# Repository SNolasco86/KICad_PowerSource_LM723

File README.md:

# Mecatronica I Fuente 18V 3A en base regulador de tensión LM723
Placa para realizar la fuente de Mecatrónica I regulable en tensión (1,2V a 18V) con limitador de corriente (0.1A a 3A).
Tambien está diseñada para poder conectarla con un voltimetro/amperimetro disponible en el mercado para ser colocada en el propio gabinete.

# Vistas

# Recursos
La placa permite generar señales eléctricas como así también recibir señales desde circuitos externos. El esqumático puede verse en este [PDF](https://github.com/SNolasco86/KICad_PowerSource_LM723/tree/main/sch/Board.pdf).

# Consideraciones de la Placa
## Gerbers
Los archivos Gerbers que están en este directorio [[link](https://github.com/SNolasco86/KICad_PowerSource_LM723/tree/main/release/)] contienen todo lo necesario para realizar la fabricación de la placa en forma industrial. Es decir, pueden ser proporcionados a cualquier fabricante de placas. En las mismas extenciones de dichos archivos se encuentran información de las capas con las que fue diseñada esta placa. Para conocer e interpretar el formato de cada extensión puede revisarse la siguiente publicación [link](https://www.proto-electronics.com/es/blog/archivos-gerber-para-qe-sirven).

## PDFs
Se exportan las diferentes capas de la placa en formato PDF de forma tal que pueda ser diseñado en forma manual. Existen diferentes métodos "caseros" con los que se puede llevar adelante la fabricación de una placa siempre y cuando el diseño lo permita. Esto quiere decir que no cualquier diseño PCB puede ser fabricado en forma manual. Esto se deben a las siguientes condiciones:
 - **Paso mínimo:** Es la mínima resolución que se considera en todo el diseño. Esto se tiene en cuenta tanto en la resolución de una pista como el margen de los pads. En el caso de intentar realizar la placa con los métodos de planchado o luz ultravioleta, aquellas placas con pasos mínimos muy pequeños son dificil de lograr.
 - **Pistas de cobre:** Los proceso de fabricación logran obtener las pistas de cobre con diferentes resoluciones según el requerimiento del cliente. En caso de querer realizar las pistas sobre una placa simple faz se debe utilizar diferentes métodos. A continuación se listan los dos métodos más comunes:
    - **Método con plancha:** Este método consiste en imprimir la capa, donde se tienen las pistas de cobre, en una hoja satinada (revistas o papel fotográfico) con una impresora laser y luego se transfiere esta impresión al pedazo de placa. En el siguiente enlace se muestra el proceso [link](https://www.neoteo.com/circuitos-impresos-el-metodo-de-la-plancha/). 
    - **Método con luz UV:** En este método se requieren más elementos complejos que el primero. Se utiliza una una hoja plástica transparente  para realizar la impresión, una pintura especial que será depositada en la placa como así también es importante tener una cámara con luz UV. Una muestra de este proceso puede verse en el siguiente enlace [link](http://uedesign.com.ar/PDFs/M%C3%A9todo_UV.pdf).

    Como se dijo anteriormente, son procesos compejos de lograr y se requiere de varios intentos. Una vez obtenida la placa con las pistas pintadas, el proceso de reacción química para remover las áreas de cobre es **peligroso** y debe tomarse todas las medidas se seguridad pertinentes. Aquí algunas referencias sobre seguridad [link](https://aulavirtual.fio.unam.edu.ar/pluginfile.php/61611/mod_resource/content/1/Seguridad%20en%20los%20laboratorios%20qu%C3%ADmicos.pdf).

 - **Máscaras anti-soldantes:** Todas las placas fabricadas industrialmente tienen, en sus capas con pistas de cobre, una máscara con una pintura anti-soldante. Esto evita que el estaño en el proceso de soldadura no se propague por todas las pistas y únicamente queden depositados en los pads. Esta casa es casi imposible de realizar en forma manual, existen técnicas pero son muy costosas y poco recomendables.
 - **Perforaciones:** Los fabricantes de placas tienen herramientas que permiten una exactitud en las perforaciones, además de complir con las secciones requeridas. En caso de realizarla manualmente este proceso podría contener errores propios de la manipulación manual y falto de precisión.

## Capas
La placa está diseñada para ser fabricada a simple faz. En los archivos [PDF](https://github.com/SNolasco86/KICad_PowerSource_LM723/tree/main/pcb/) de fabricación se pueden identificar dos capas:
 - **Capa Superior [[minilab-F.Cu.pdf](https://github.com/SNolasco86/KICad_PowerSource_LM723/blob/main/pcb/Top.pdf)]:** En esta capa se colocarán los componentes electrónicos y en caso de fabricar manualmente la placa, se deberá insertar los cables-puentes de la placa. Estos "puentes" emulan las coneciones de la capa inferior. 
 - **Capa inferior[[minilab-B.Cu.pdf](https://github.com/SNolasco86/KICad_PowerSource_LM723/blob/main/pcb/Bottom.pdf)]:** Es la capa dónde se trandrán las pistas de cobre y se realizarán las soldaduras.

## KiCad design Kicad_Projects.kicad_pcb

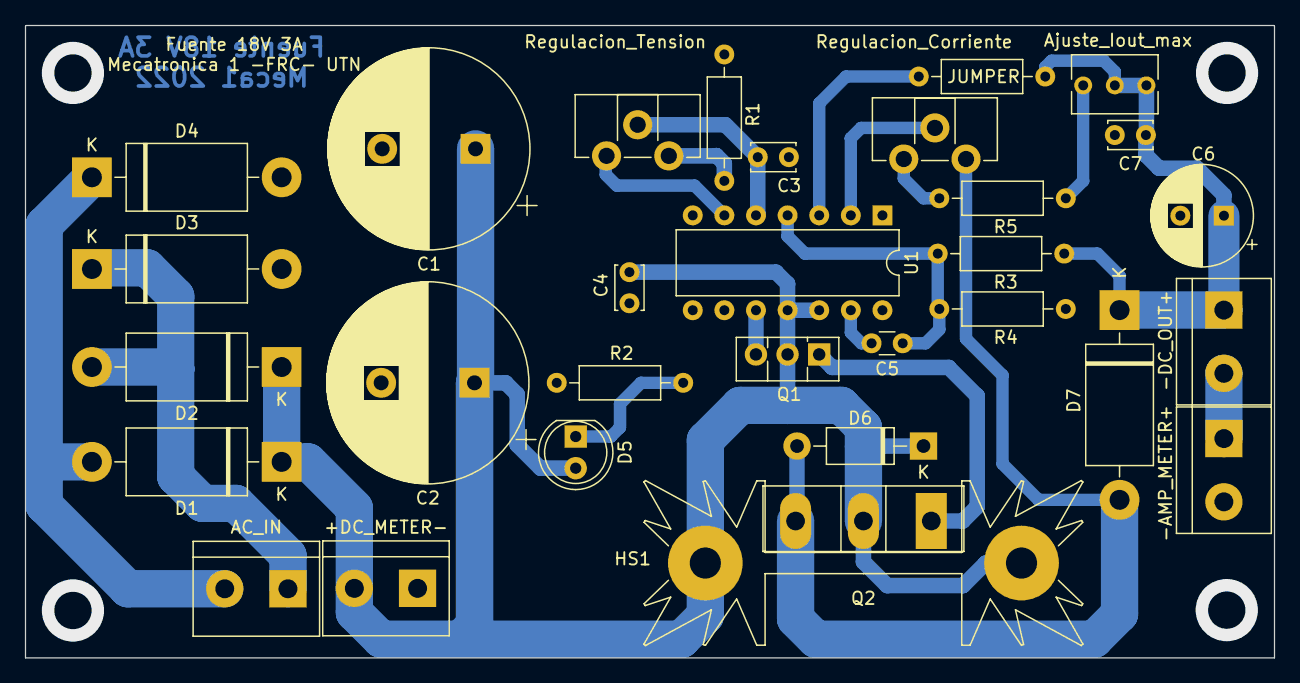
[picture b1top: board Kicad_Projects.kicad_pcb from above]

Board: 2 copper layers, 100.3 x 50.8 mm, 31 parts (0 on the bottom side), 19 nets.

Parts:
+DC_METER-: Vcc_Volt/Amper; TerminalBlock_bornier-2_P5.08mm
-AMP_METER+: Amperimetro; TerminalBlock_bornier-2_P5.08mm
-DC_OUT+: Vout; TerminalBlock_bornier-2_P5.08mm
AC_IN: Ent. 15Vca; TerminalBlock_bornier-2_P5.08mm
Ajuste_Iout_max: 500; Potentiometer_Bourns_3266Y_Vertical
C1, C2: 2200u; CP_Radial_D16.0mm_P7.50mm
C3, C4, C7: 100n; C_Disc_D3.4mm_W2.1mm_P2.50mm
C5: 470p; C_Disc_D3.0mm_W1.6mm_P2.50mm
C6: 100u; CP_Radial_D8.0mm_P3.50mm
D1, D2, D3, D4, D7: 1N5404; D_DO-201AD_P15.24mm_Horizontal
D5: LED; LED_D5.0mm
D6: 1N4007; D_DO-41_SOD81_P10.16mm_Horizontal
HS1: Heatsink_Pad; Heatsink_Fischer_SK104-STC-STIC_35x13mm_2xDrill2.5mm
JUMPER: Jumper_2_Bridged; R_Axial_DIN0207_L6.3mm_D2.5mm_P10.16mm_Horizontal
Q1: BD137; TO-126-3_Vertical
Q2: TIP3055G; TO-247-3_Vertical
R1: 470; R_Axial_DIN0207_L6.3mm_D2.5mm_P10.16mm_Horizontal
R2: 1k8; R_Axial_DIN0207_L6.3mm_D2.5mm_P10.16mm_Horizontal
R3: 1K8; R_Axial_DIN0207_L6.3mm_D2.5mm_P10.16mm_Horizontal
R4: 1K2; R_Axial_DIN0207_L6.3mm_D2.5mm_P10.16mm_Horizontal
R5: 1200; R_Axial_DIN0207_L6.3mm_D2.5mm_P10.16mm_Horizontal
Regulacion_Corriente: 500; Potentiometer_ACP_CA9-H2,5_Horizontal
Regulacion_Tension: 10k; Potentiometer_ACP_CA9-H2,5_Horizontal
U1: LM723_DIP14; DIP-14_W7.62mm

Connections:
+VDC: +DC_METER-.2, C1.1, C2.1, C4.1, D1.1 (K), D2.1 (K), D5.2 (A), D6.1 (K), HS1.1, Q1.2 (C), Q2.2 (C), U1.11 (VC), U1.12 (V+)
AC_F: AC_IN.2, D1.2 (A), D4.1 (K)
AC_N: AC_IN.1, D2.2 (A), D3.1 (K)
GND: +DC_METER-.1, -AMP_METER+.2, C1.2, C2.2, C3.2, C4.2, C6.2, C7.2, D3.2 (A), D4.2 (A), R1.2, R2.2, R4.2, U1.7 (V-)
unnamed: Ajuste_Iout_max.1, R5.2
unnamed: C3.1, Regulacion_Tension.2, U1.5 (+)
unnamed: C5.1, R3.2, R4.1, U1.4 (-)
unnamed: C5.2, U1.13 (FC)
unnamed: D5.1 (K), R2.1
unnamed: Q1.1 (E), Q2.1 (B)
unnamed: Q1.3 (B), U1.10 (Vout)
unnamed: R1.1, Regulacion_Tension.3
unnamed: R5.1, Regulacion_Corriente.1
unnamed: Regulacion_Corriente.2, U1.2 (ILIM)
unnamed: Regulacion_Tension.1, U1.6 (VREF)
unnamed: JUMPER.2 (B), U1.3 (CSEN)
TBJ_Out: D6.2 (A), D7.2 (A), Q2.3 (E), Regulacion_Corriente.3
Vout: -DC_OUT+.1, Ajuste_Iout_max.2, Ajuste_Iout_max.3, C6.1, C7.1, D7.1 (K), JUMPER.1 (A), R3.1
Vout_amp: -AMP_METER+.1, -DC_OUT+.2

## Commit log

2022-03-11 Fuente basica
2022-03-13 Mejoras en PCB
2022-03-14 Agregado de jumper
2022-03-14 Se corrigio espejo en leyenda
2022-03-25 cambio jumper y BOM en .csv
2022-04-03 Agrego modelo MEcanico .wrl
2022-04-03 Agrego modelo .STEP
2022-05-12 Agrego plantilla de componentes .pdf .svg
2022-05-17 PCB y gerbers actualizado
2022-05-17 agregado en F_silk jumper
2022-05-29 Agrego imagenes /shape3D
2022-05-29 PCB actualizado
2022-05-29 Agrego schematic
2022-05-29 Agrego pcb para planchar
2022-05-29 Actualizo imagenes
2022-05-29 pcb nuevo
2022-06-02 Actualizacion Jumper 01/06
